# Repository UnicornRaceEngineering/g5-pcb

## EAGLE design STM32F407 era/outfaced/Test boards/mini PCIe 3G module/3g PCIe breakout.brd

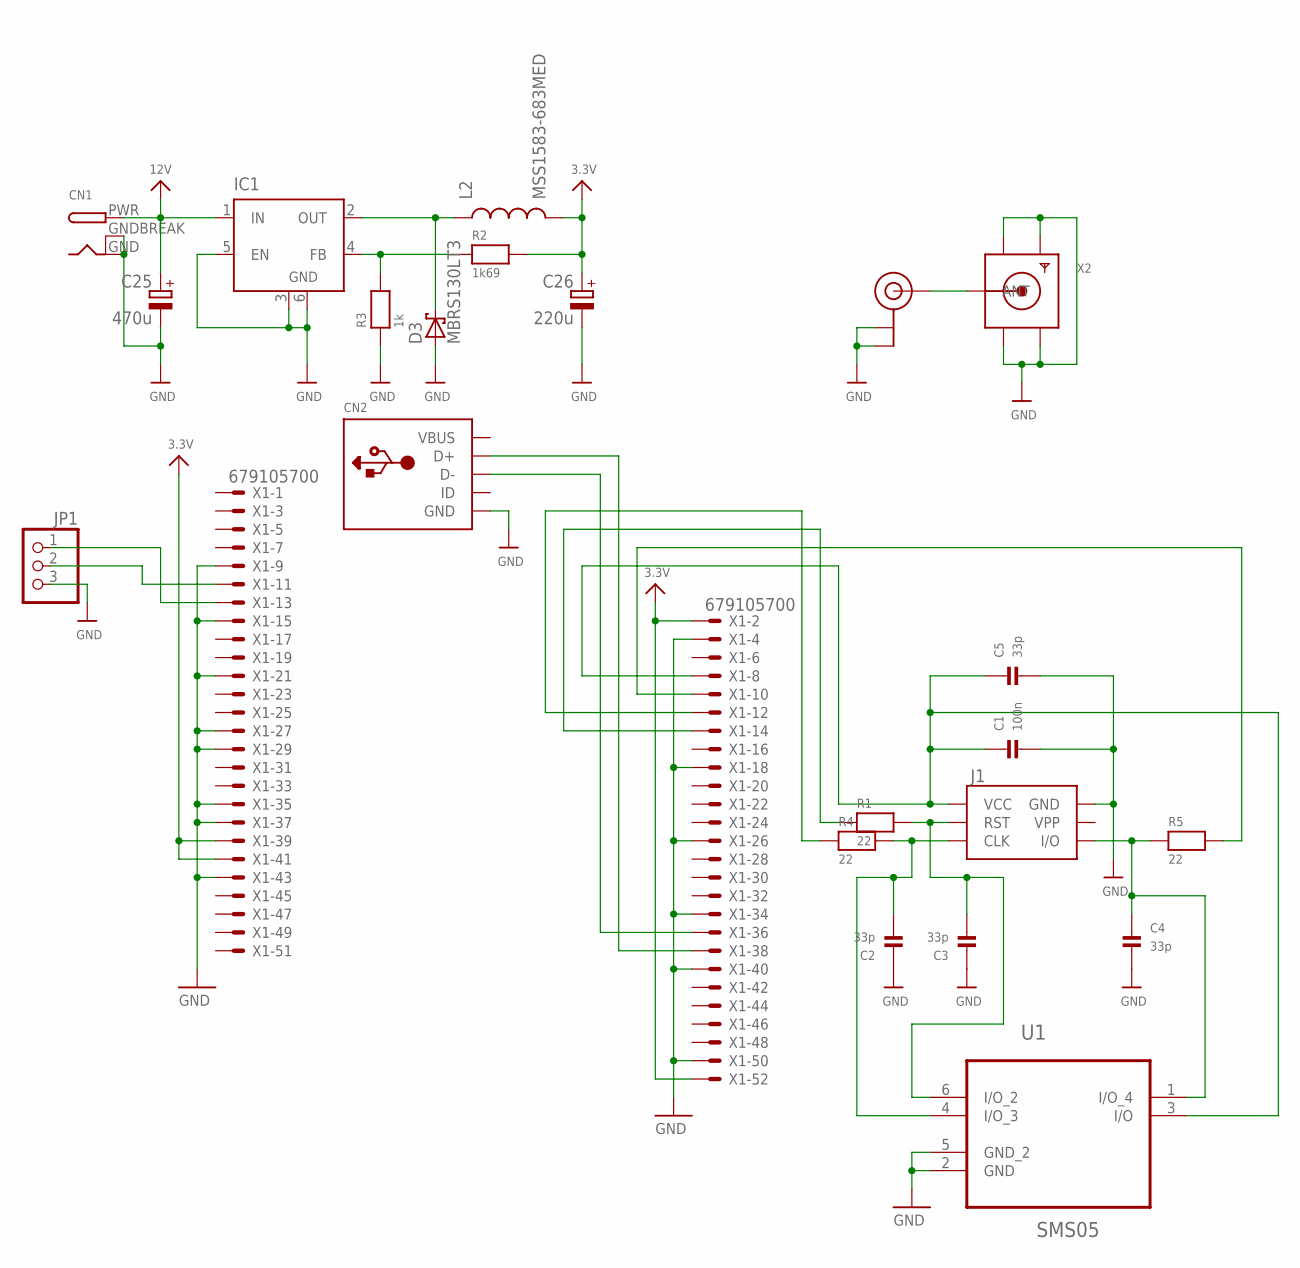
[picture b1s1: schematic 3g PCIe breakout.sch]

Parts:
C1: 100n; _0603
C2, C3, C4, C5: 33p; _0603
C25: 470u; 153CLV-1012
C26: 220u; 153CLV-1012
CN1: DCBARRELPTH; DCJACK_2MM_PTH
CN2: USBMINIB; USB-MINIB
D3: MBRS130LT3; SMB
IC1: LM2596S; TO263-5
J1: SIMHOLDERSIM; SIMHOLDER
JP1: PINHD-1X3; 1X03
L2: MSS1583-683MED; CDRH125
R1, R4, R5: 22; _0603
R2: 1k69; _0603
R3: 1k; _0603
U1: SMS05; SOT95P280X145-6N
U$12: U.FL
X1: 679105700
X2: SMACONNECTOR; SMA90_DIP

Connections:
3.3V: C26.+, L2.2, R2.2, X1.2, X1.39, X1.41, X1.52
12V: C25.+, CN1.PWR, IC1.1 (IN)
GND: C1.2, C2.1, C3.1, C4.2, C5.2, C25.-, C26.-, CN1.GND, CN1.GNDBREAK, CN2.GND, D3.A, IC1.3 (GND), IC1.5 (EN), IC1.6 (GND), J1.C5 (GND), JP1.3, R3.1, U1.2 (GND), U1.5 (GND_2), U$12.1 (GND), U$12.2 (GND), X1.4, X1.9, X1.15, X1.18, X1.21, X1.26, X1.27, X1.29, X1.34, X1.35, X1.37, X1.40, X1.43, X1.50, X2.GND1, X2.GND2, X2.GND3, X2.GND4
unnamed: CN2.D+, X1.38
unnamed: CN2.D-, X1.36
unnamed: JP1.1, X1.13
unnamed: JP1.2, X1.11
unnamed: C3.2, J1.C2 (RST), R1.2, U1.6 (I/O_2)
unnamed: D3.C, IC1.2 (OUT), L2.1
unnamed: C2.2, J1.C3 (CLK), R4.2, U1.4 (I/O_3)
unnamed: C4.1, J1.C7 (I/O), R5.1, U1.1 (I/O_4)
unnamed: IC1.4 (FB), R2.1, R3.2
unnamed: C1.1, C5.1, J1.C1 (VCC), U1.3 (I/O), X1.8
unnamed: R5.2, X1.10
unnamed: R1.1, X1.14
unnamed: R4.1, X1.12
unnamed: U$12.3 (SIGNAL), X2.ANTENNA (ANT)
VBUS: CN2.VBUS

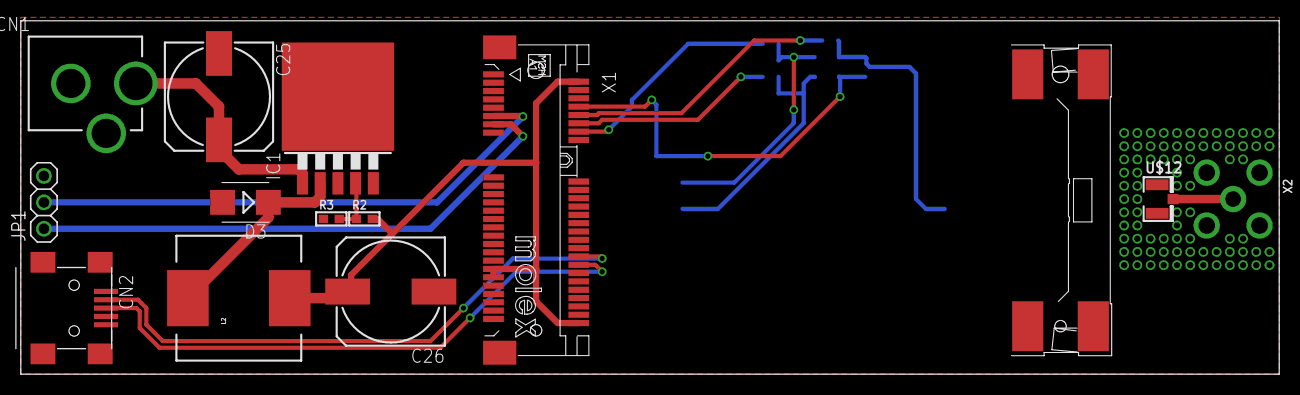
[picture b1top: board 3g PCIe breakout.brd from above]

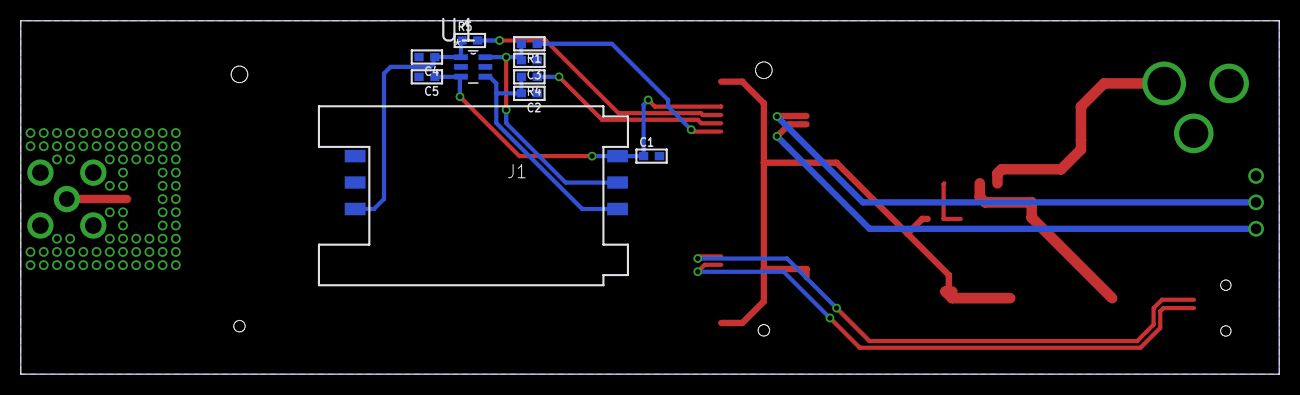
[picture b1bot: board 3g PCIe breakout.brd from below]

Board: 2 copper layers, 120.9 x 34.0 mm, 23 parts (10 on the bottom side), 17 nets.

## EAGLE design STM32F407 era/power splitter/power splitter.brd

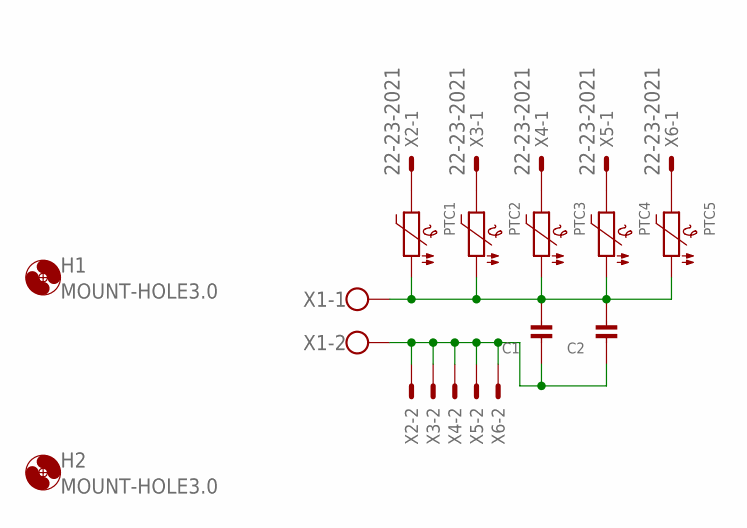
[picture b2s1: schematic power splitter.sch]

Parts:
C1, C2: CAP_CERAMIC_0805; _0805
H1, H2: MOUNT-HOLE3.0; 3,0
PTC1, PTC2, PTC3, PTC4, PTC5: PTC1206; 1206
X1: W237-102
X2, X3, X4, X5, X6: 22-23-2021

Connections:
unnamed: PTC1.2, X2.1
unnamed: PTC2.2, X3.1
unnamed: PTC3.2, X4.1
unnamed: PTC4.2, X5.1
unnamed: PTC5.2, X6.1
unnamed: C1.2, C2.2, PTC1.1, PTC2.1, PTC3.1, PTC4.1, PTC5.1, X1.1
unnamed: C1.1, C2.1, X1.2, X2.2, X3.2, X4.2, X5.2, X6.2

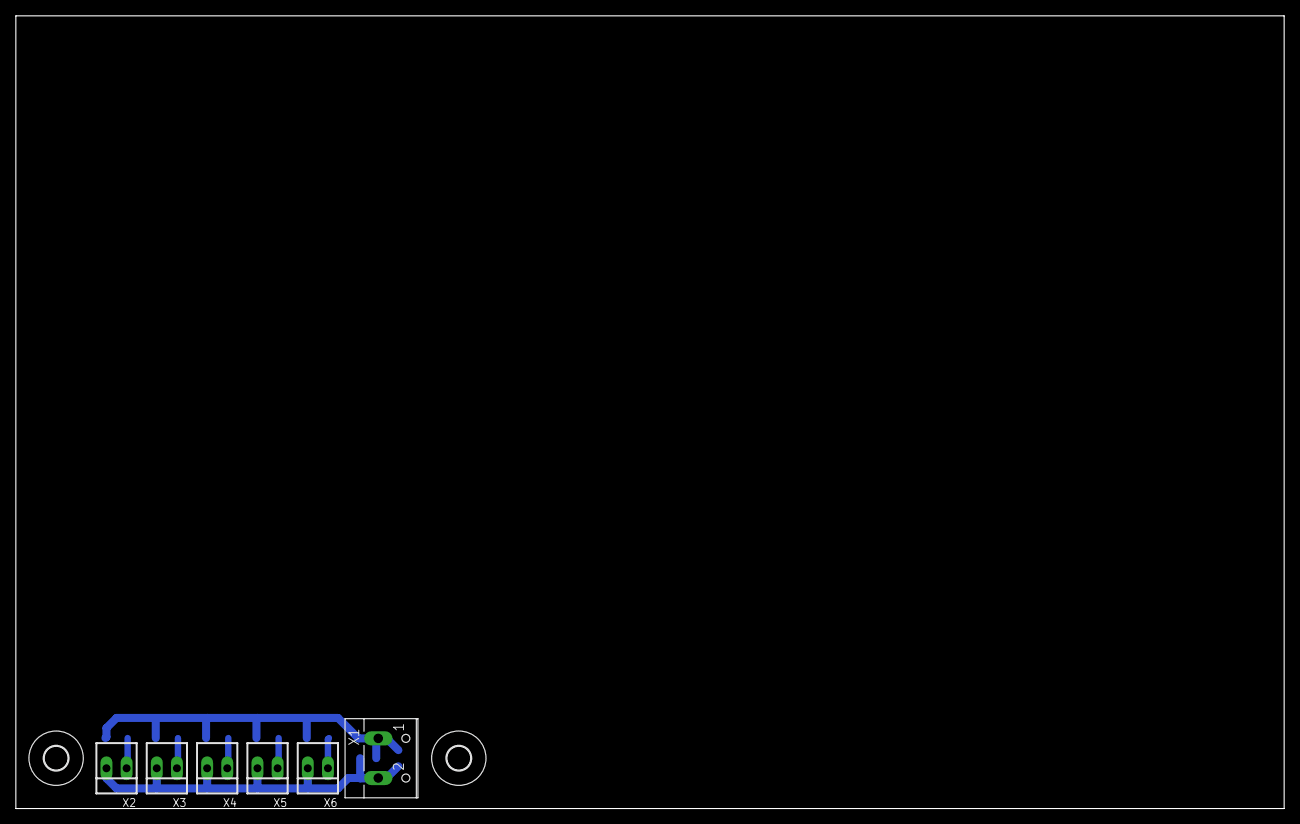
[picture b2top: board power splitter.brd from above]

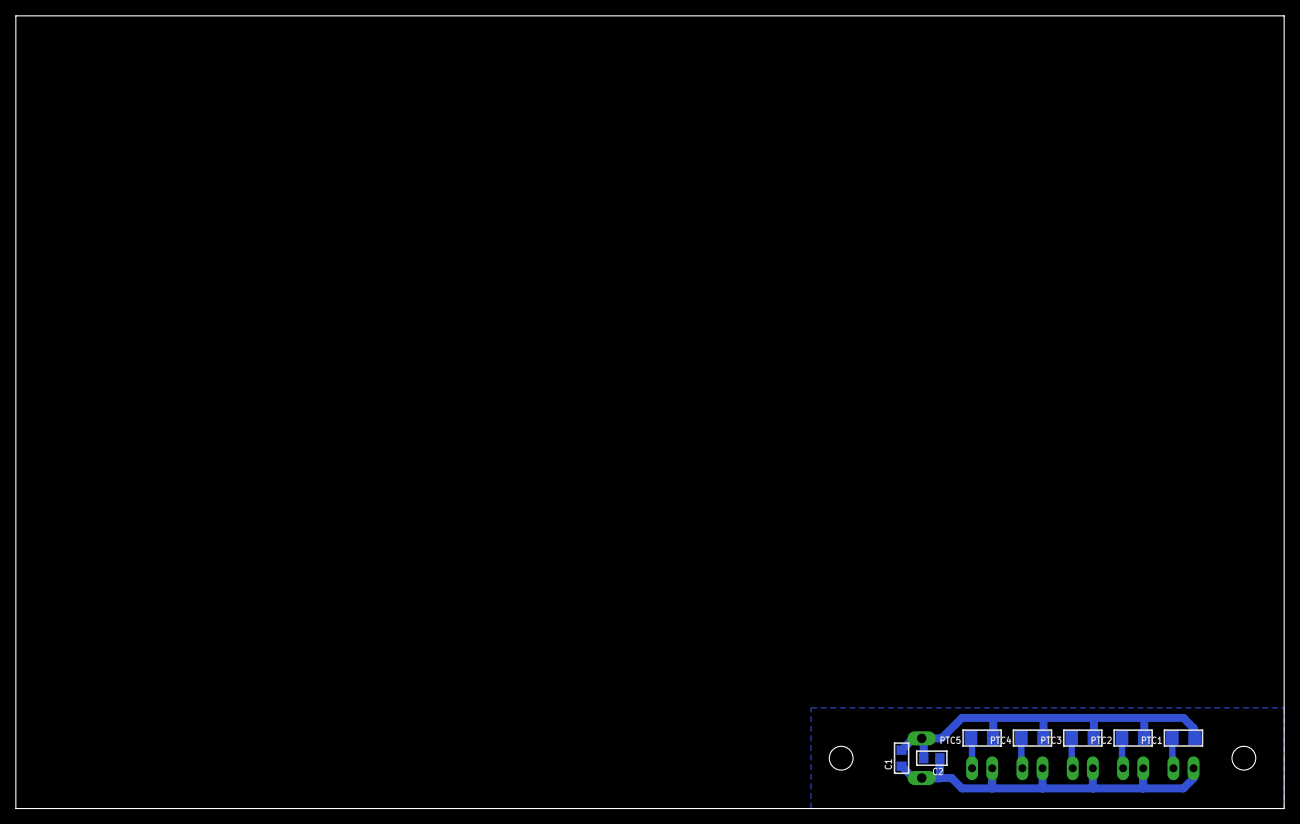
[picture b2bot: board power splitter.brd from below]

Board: 2 copper layers, 160.0 x 100.0 mm, 15 parts (7 on the bottom side), 7 nets.

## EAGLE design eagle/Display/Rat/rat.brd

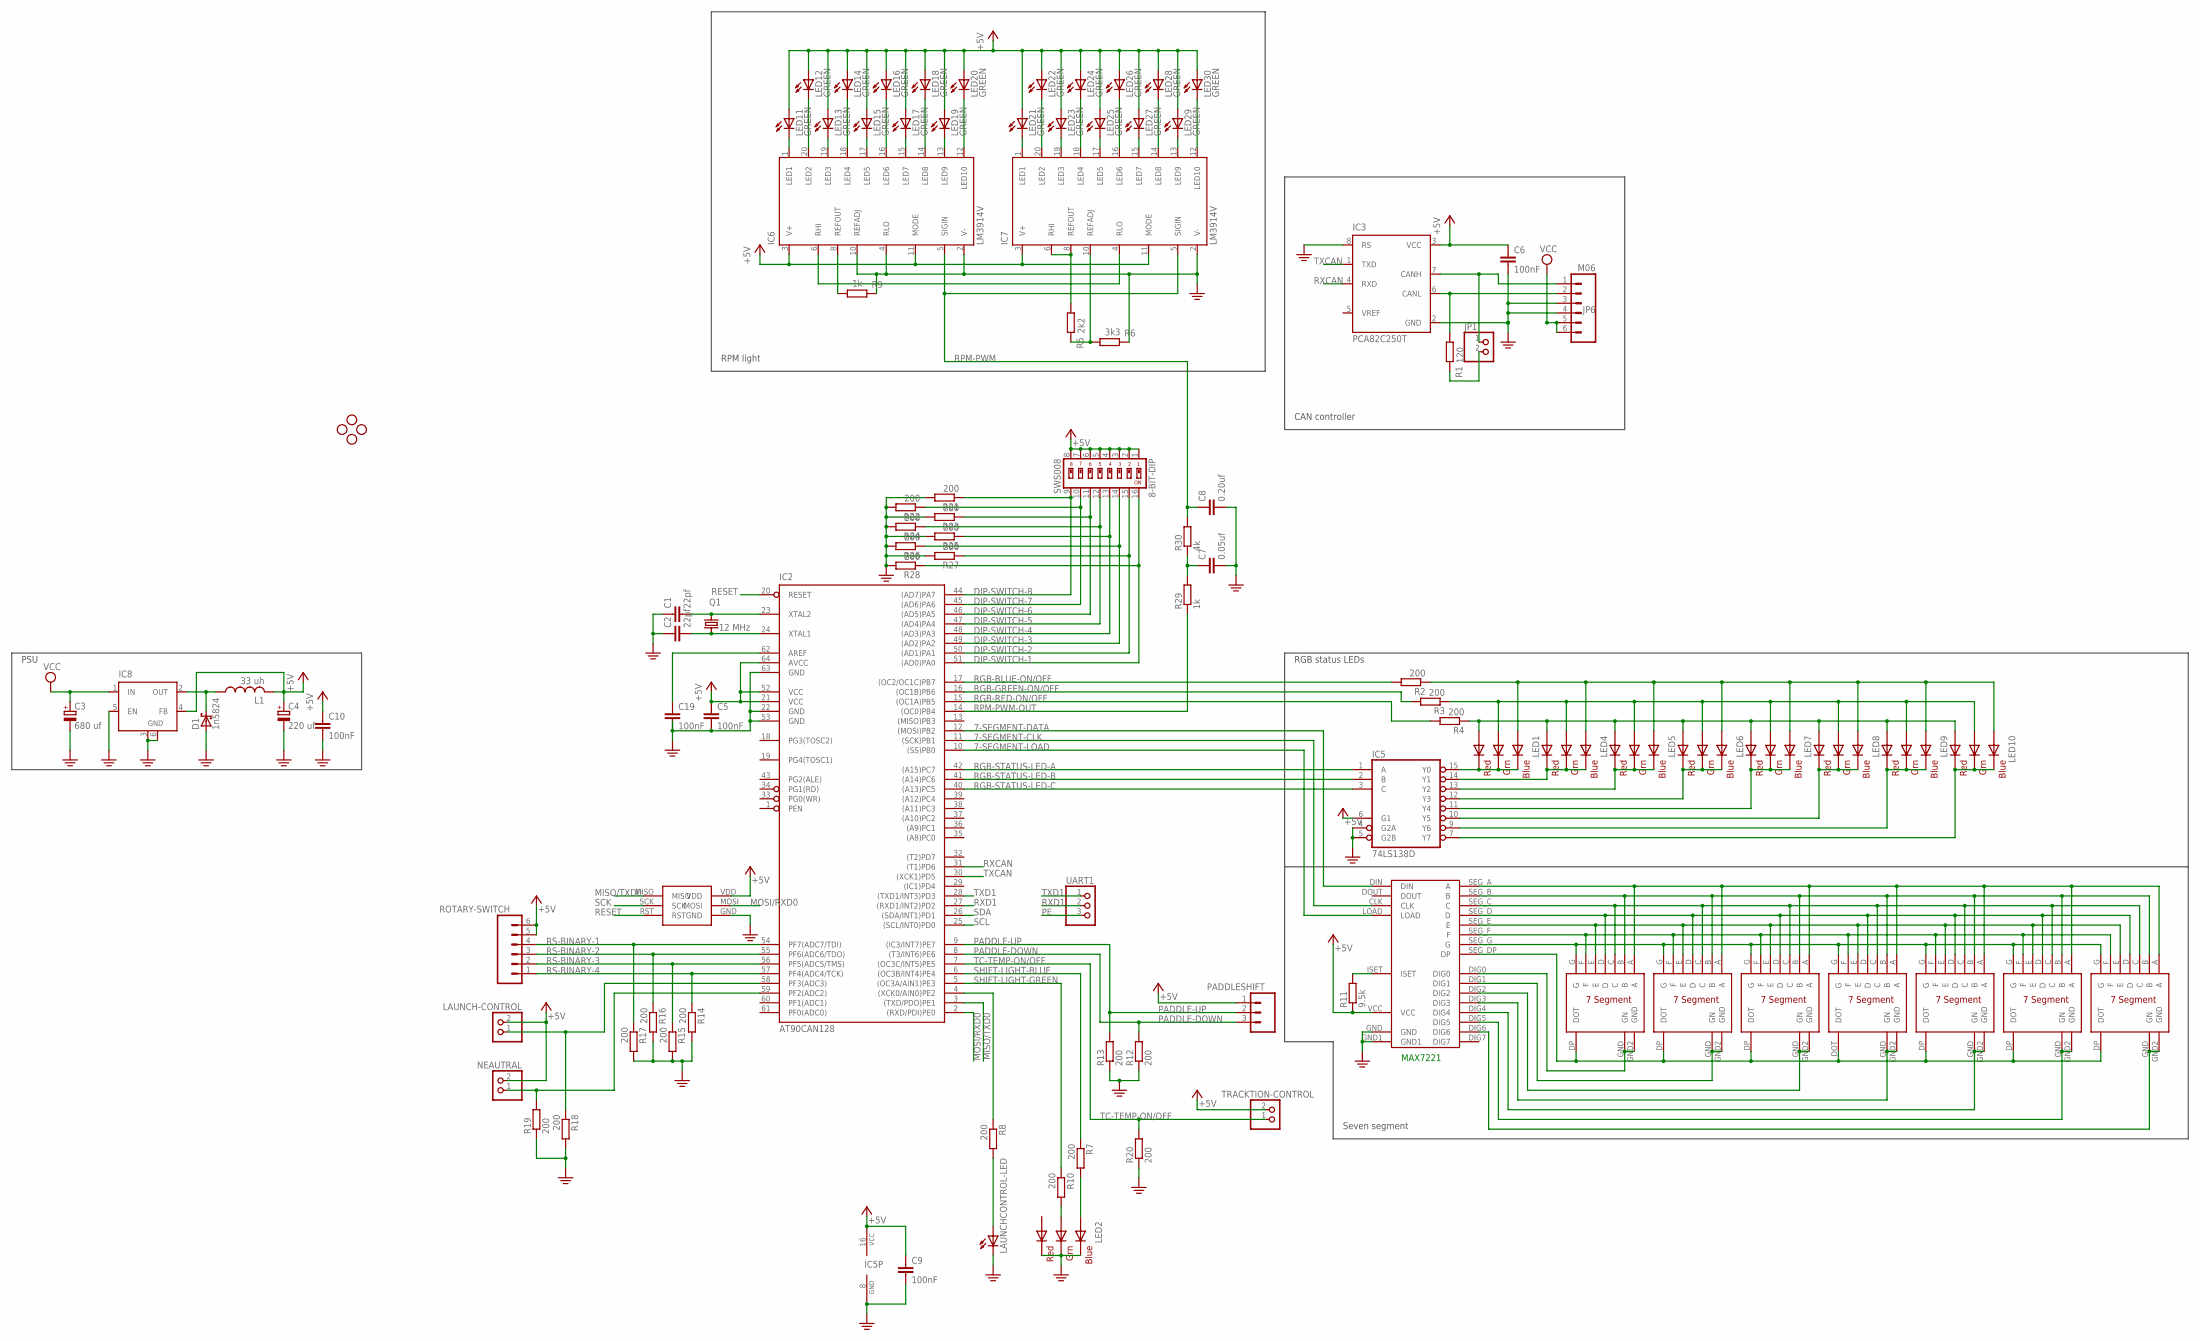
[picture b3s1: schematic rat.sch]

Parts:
8-BIT-DIP: SWS008; SMS-008
C1, C2: 22pf; C0603K
C3: 680 uf; E5-10,5
C4: 220 uf; E2,5-7
C5, C6, C9, C10, C19: 100nF; C0603K
C7: 0.05uf; C0603K
C8: 0.20uf; C0603K
D1: 1n5824; P6T15
IC2: AT90CAN128; TQFP64
IC3: PCA82C250T; SO8
IC5: 74LS138D; SO16
IC6, IC7: LM3914V; PLCC20S
IC8: LM2596S; TO263-5
JP1: PINHD-1X2; 1X02
JP2, JP3, JP4, JP5: STAND-OFF
JP6: M06; S6B_PH
L1: 33 uh; TFI0410
LAUNCH-CONTROL: JST_2PIN-SMT-RA; JST-PH-2-SMT-RA
LAUNCHCONTROL-LED: LEDSMT1206; 1206
LED1, LED2, LED4, LED5, LED6, LED7, LED8, LED9, LED10: RGBLED5050
LED11, LED12, LED13, LED14, LED15, LED16, LED17, LED18, LED19, LED20, LED21, LED22, LED23, LED24, LED25, LED26, LED27, LED28, LED29, LED30: GREEN; 1206
MAX7221: MAX7221-SMD; MAX7221
NEAUTRAL: JST_2PIN-SMT-RA; JST-PH-2-SMT-RA
PADDLESHIFT: M03; S3B-PH
Q1: 12 MHz; HC49U70
R1: 120; R0603
R2, R3, R4, R7, R8, R10, R12, R13, R14, R15, R16, R17, R18, R19, R20, R21, R22, R23, R24, R25, R26, R27, R28: 200; R0603
R5: 2k2; R0603
R6: 3k3; R0603
R9, R29: 1k; R0603
R11: 9.5k; R0603
R30: 4k; R0603
ROTARY-SWITCH: M06; S6B_PH
TRACKTION-CONTROL: JST_2PIN-SMT-RA; JST-PH-2-SMT-RA
U$2, U$3, U$4, U$6, U$7, U$8: REDSEVENSEGMENT; REDSEGMENT
U$5: BIGSEVENSEGMENT
U$9: ISP-HEADER
UART1: PINHD-1X3; 1X03

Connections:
7-SEGMENT-CLK: IC2.11 ((SCK)PB1), MAX7221.CLK
7-SEGMENT-DATA: IC2.12 ((MOSI)PB2), MAX7221.DIN
7-SEGMENT-LOAD: IC2.10 ((SS)PB0), MAX7221.LOAD
+5V: 8-BIT-DIP.1, 8-BIT-DIP.2, 8-BIT-DIP.3, 8-BIT-DIP.4, 8-BIT-DIP.5, 8-BIT-DIP.6, 8-BIT-DIP.7, 8-BIT-DIP.8, C4.+, C5.1, C6.1, C9.1, C10.1, IC2.21 (VCC), IC2.52 (VCC), IC2.64 (AVCC), IC3.3 (VCC), IC5.6 (G1), IC5.16 (VCC), IC6.3 (V+), IC6.11 (MODE), IC7.3 (V+), IC7.11 (MODE), IC8.4 (FB), L1.2, LAUNCH-CONTROL.2 (1), LED11.A, LED12.A, LED13.A, LED14.A, LED15.A, LED16.A, LED17.A, LED18.A, LED19.A, LED20.A, LED21.A, LED22.A, LED23.A, LED24.A, LED25.A, LED26.A, LED27.A, LED28.A, LED29.A, LED30.A, MAX7221.VCC, NEAUTRAL.2 (1), PADDLESHIFT.1, R11.1, ROTARY-SWITCH.5, ROTARY-SWITCH.6, TRACKTION-CONTROL.2 (1), U$9.VDD
CANJUMP1: IC3.7 (CANH), JP1.1, JP6.1
CANJUMP2: JP1.2, R1.2
DIP-SWITCH-1: 8-BIT-DIP.16, IC2.51 ((AD0)PA0), R28.1
DIP-SWITCH-2: 8-BIT-DIP.15, IC2.50 ((AD1)PA1), R27.1
DIP-SWITCH-3: 8-BIT-DIP.14, IC2.49 ((AD2)PA2), R26.1
DIP-SWITCH-4: 8-BIT-DIP.13, IC2.48 ((AD3)PA3), R25.1
DIP-SWITCH-5: 8-BIT-DIP.12, IC2.47 ((AD4)PA4), R24.1
DIP-SWITCH-6: 8-BIT-DIP.11, IC2.46 ((AD5)PA5), R23.1
DIP-SWITCH-7: 8-BIT-DIP.10, IC2.45 ((AD6)PA6), R22.1
DIP-SWITCH-8: 8-BIT-DIP.9, IC2.44 ((AD7)PA7), R21.1
MISO/TXD0: IC2.3 ((TXD/PDO)PE1), U$9.MISO
MOSI/RXD0: IC2.2 ((RXD/PDI)PE0), U$9.MOSI
unnamed: C2.2, IC2.24 (XTAL1), Q1.1
unnamed: C1.2, IC2.23 (XTAL2), Q1.2
unnamed: MAX7221.SEG_A (A), U$2.A, U$3.A, U$4.A, U$5.A, U$6.A, U$7.A, U$8.A
unnamed: MAX7221.SEG_B (B), U$2.B, U$3.B, U$4.B, U$5.B, U$6.B, U$7.B, U$8.B
unnamed: MAX7221.SEG_C (C), U$2.C, U$3.C, U$4.C, U$5.C, U$6.C, U$7.C, U$8.C
unnamed: C19.1, IC2.62 (AREF)
unnamed: MAX7221.SEG_D (D), U$2.D, U$3.D, U$4.D, U$5.D, U$6.D, U$7.D, U$8.D
unnamed: MAX7221.SEG_E (E), U$2.E, U$3.E, U$4.E, U$5.E, U$6.E, U$7.E, U$8.E
unnamed: MAX7221.SEG_F (F), U$2.F, U$3.F, U$4.F, U$5.F, U$6.F, U$7.F, U$8.F
unnamed: MAX7221.SEG_G (G), U$2.G, U$3.G, U$4.G, U$5.G, U$6.G, U$7.G, U$8.G
unnamed: MAX7221.DIG0, U$2.GND (GN), U$2.GND2 (GND)
unnamed: MAX7221.DIG1, U$3.GND (GN), U$3.GND2 (GND)
unnamed: MAX7221.DIG2, U$4.GND (GN), U$4.GND2 (GND)
unnamed: MAX7221.DIG3, U$5.GND (GN), U$5.GND2 (GND)
unnamed: MAX7221.DIG4, U$6.GND (GN), U$6.GND2 (GND)
unnamed: MAX7221.DIG5, U$7.GND (GN), U$7.GND2 (GND)
unnamed: MAX7221.DIG6, U$8.GND (GN), U$8.GND2 (GND)
unnamed: MAX7221.SEG_DP (DP), U$2.DP (DOT), U$3.DP (DOT), U$4.DP (DOT), U$5.DOT, U$6.DP (DOT), U$7.DP (DOT), U$8.DP (DOT)
unnamed: C7.1, R29.2, R30.1
unnamed: MAX7221.ISET, R11.2
unnamed: IC2.59 (PF2(ADC2)), NEAUTRAL.1 (2), R19.2
unnamed: LED1.2 (RED_A), LED4.2 (RED_A), LED5.2 (RED_A), LED6.2 (RED_A), LED7.2 (RED_A), LED8.2 (RED_A), LED9.2 (RED_A), LED10.2 (RED_A), R4.1
unnamed: LED1.1 (GREEN_A), LED4.1 (GREEN_A), LED5.1 (GREEN_A), LED6.1 (GREEN_A), LED7.1 (GREEN_A), LED8.1 (GREEN_A), LED9.1 (GREEN_A), LED10.1 (GREEN_A), R3.1
unnamed: LED1.3 (BLUE_A), LED4.3 (BLUE_A), LED5.3 (BLUE_A), LED6.3 (BLUE_A), LED7.3 (BLUE_A), LED8.3 (BLUE_A), LED9.3 (BLUE_A), LED10.3 (BLUE_A), R2.1
unnamed: IC5.15 (Y0), LED1.4 (BLUE_C), LED1.5 (RED_C), LED1.6 (GREEN_C)
unnamed: IC5.14 (Y1), LED4.4 (BLUE_C), LED4.5 (RED_C), LED4.6 (GREEN_C)
unnamed: IC5.13 (Y2), LED5.4 (BLUE_C), LED5.5 (RED_C), LED5.6 (GREEN_C)
unnamed: IC5.12 (Y3), LED6.4 (BLUE_C), LED6.5 (RED_C), LED6.6 (GREEN_C)
unnamed: IC5.11 (Y4), LED7.4 (BLUE_C), LED7.5 (RED_C), LED7.6 (GREEN_C)
unnamed: IC5.10 (Y5), LED8.4 (BLUE_C), LED8.5 (RED_C), LED8.6 (GREEN_C)
unnamed: IC5.9 (Y6), LED9.4 (BLUE_C), LED9.5 (RED_C), LED9.6 (GREEN_C)
unnamed: IC5.7 (Y7), LED10.4 (BLUE_C), LED10.5 (RED_C), LED10.6 (GREEN_C)
unnamed: D1.C, IC8.2 (OUT), L1.1
unnamed: IC6.1 (LED1), LED11.C
unnamed: IC6.20 (LED2), LED12.C
unnamed: IC6.19 (LED3), LED13.C
unnamed: IC3.6 (CANL), JP6.2, R1.1
unnamed: IC6.18 (LED4), LED14.C
unnamed: IC6.17 (LED5), LED15.C
unnamed: IC6.16 (LED6), LED16.C
unnamed: IC6.15 (LED7), LED17.C
unnamed: IC6.14 (LED8), LED18.C
unnamed: IC6.13 (LED9), LED19.C
unnamed: IC6.12 (LED10), LED20.C
unnamed: IC7.1 (LED1), LED21.C
unnamed: IC7.20 (LED2), LED22.C
unnamed: IC7.19 (LED3), LED23.C
unnamed: IC7.18 (LED4), LED24.C
unnamed: IC7.17 (LED5), LED25.C
unnamed: IC7.16 (LED6), LED26.C
unnamed: IC7.15 (LED7), LED27.C
unnamed: IC7.14 (LED8), LED28.C
unnamed: IC7.13 (LED9), LED29.C
unnamed: IC7.12 (LED10), LED30.C
unnamed: IC2.58 (PF3(ADC3)), LAUNCH-CONTROL.1 (2), R18.1
unnamed: IC6.6 (RHI), IC7.4 (RLO)
unnamed: IC7.6 (RHI), IC7.8 (REFOUT), R5.1
unnamed: IC7.10 (REFADJ), R5.2, R6.1
unnamed: IC6.8 (REFOUT), R9.1
unnamed: LED2.3 (BLUE_A), R7.2
unnamed: LED2.1 (GREEN_A), R10.2
unnamed: LAUNCHCONTROL-LED.A, R8.2
unnamed: IC2.4 ((XCK0/AIN0)PE2), R8.1
PADDLE-DOWN: IC2.8 ((T3/INT6)PE6), PADDLESHIFT.3, R12.2
PADDLE-UP: IC2.9 ((IC3/INT7)PE7), PADDLESHIFT.2, R13.2
PE: C1.1, C2.1, C3.-, C4.-, C5.2, C6.2, C7.2, C8.2, C9.2, C10.2, C19.2, D1.A, IC2.22 (GND), IC2.53 (GND), IC2.63 (GND), IC3.2 (GND), IC3.8 (RS), IC5.4 (G2A), IC5.5 (G2B), IC5.8 (GND), IC6.2 (V-), IC6.4 (RLO), IC6.10 (REFADJ), IC7.2 (V-), IC8.3 (GND), IC8.5 (EN), IC8.6 (GND), JP6.3, JP6.4, LAUNCHCONTROL-LED.C, LED2.4 (BLUE_C), LED2.5 (RED_C), LED2.6 (GREEN_C), MAX7221.GND, MAX7221.GND1, R6.2, R9.2, R12.1, R13.1, R14.2, R15.2, R16.2, R17.2, R18.2, R19.1, R20.1, R21.2, R22.2, R23.2, R24.2, R25.2, R26.2, R27.2, R28.2, U$9.GND, UART1.3
RESET: IC2.20 (RESET), U$9.RST
RGB-BLUE-ON/OFF: IC2.17 ((OC2/OC1C)PB7), R2.2
RGB-GREEN-ON/OFF: IC2.16 ((OC1B)PB6), R3.2
RGB-RED-ON/OFF: IC2.15 ((OC1A)PB5), R4.2
RGB-STATUS-LED-A: IC2.42 ((A15)PC7), IC5.1 (A)
RGB-STATUS-LED-B: IC2.41 ((A14)PC6), IC5.2 (B)
RGB-STATUS-LED-C: IC2.40 ((A13)PC5), IC5.3 (C)
RPM-PWM: C8.1, IC6.5 (SIGIN), IC7.5 (SIGIN), R30.2
RPM-PWM-OUT: IC2.14 ((OC0)PB4), R29.1
RS-BINARY-1: IC2.54 (PF7(ADC7/TDI)), R17.1, ROTARY-SWITCH.4
RS-BINARY-2: IC2.55 (PF6(ADC6/TDO)), R16.1, ROTARY-SWITCH.3
RS-BINARY-3: IC2.56 (PF5(ADC5/TMS)), R15.1, ROTARY-SWITCH.2
RS-BINARY-4: IC2.57 (PF4(ADC4/TCK)), R14.1, ROTARY-SWITCH.1
RXCAN: IC2.31 ((T1)PD6), IC3.4 (RXD)
RXD1: IC2.27 ((RXD1/INT2)PD2), UART1.2
SCK: U$9.SCK
SCL: IC2.25 ((SCL/INT0)PD0)
SDA: IC2.26 ((SDA/INT1)PD1)
SHIFT-LIGHT-BLUE: IC2.6 ((OC3B/INT4)PE4), R7.1
SHIFT-LIGHT-GREEN: IC2.5 ((OC3A/AIN1)PE3), R10.1
TC-TEMP-ON/OFF: IC2.7 ((OC3C/INT5)PE5), R20.2, TRACKTION-CONTROL.1 (2)
TXCAN: IC2.30 ((XCK1)PD5), IC3.1 (TXD)
TXD1: IC2.28 ((TXD1/INT3)PD3), UART1.1
VCC: C3.+, IC8.1 (IN), JP6.5, JP6.6

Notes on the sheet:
MAX7221
RPM light
CAN controller
RGB status LEDs
Seven segment
PSU

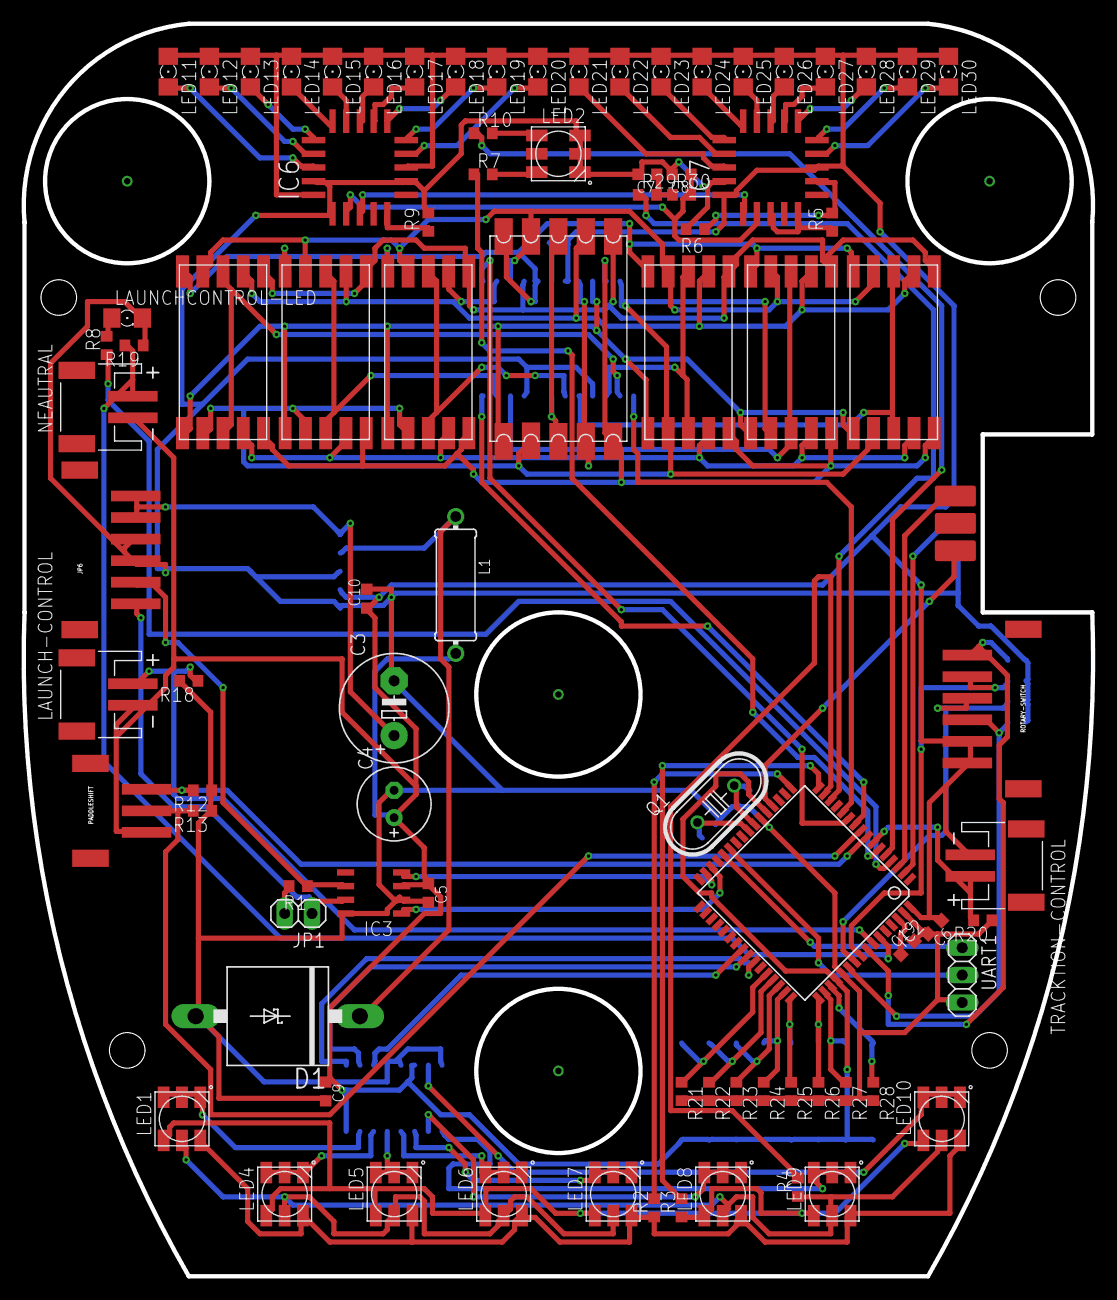
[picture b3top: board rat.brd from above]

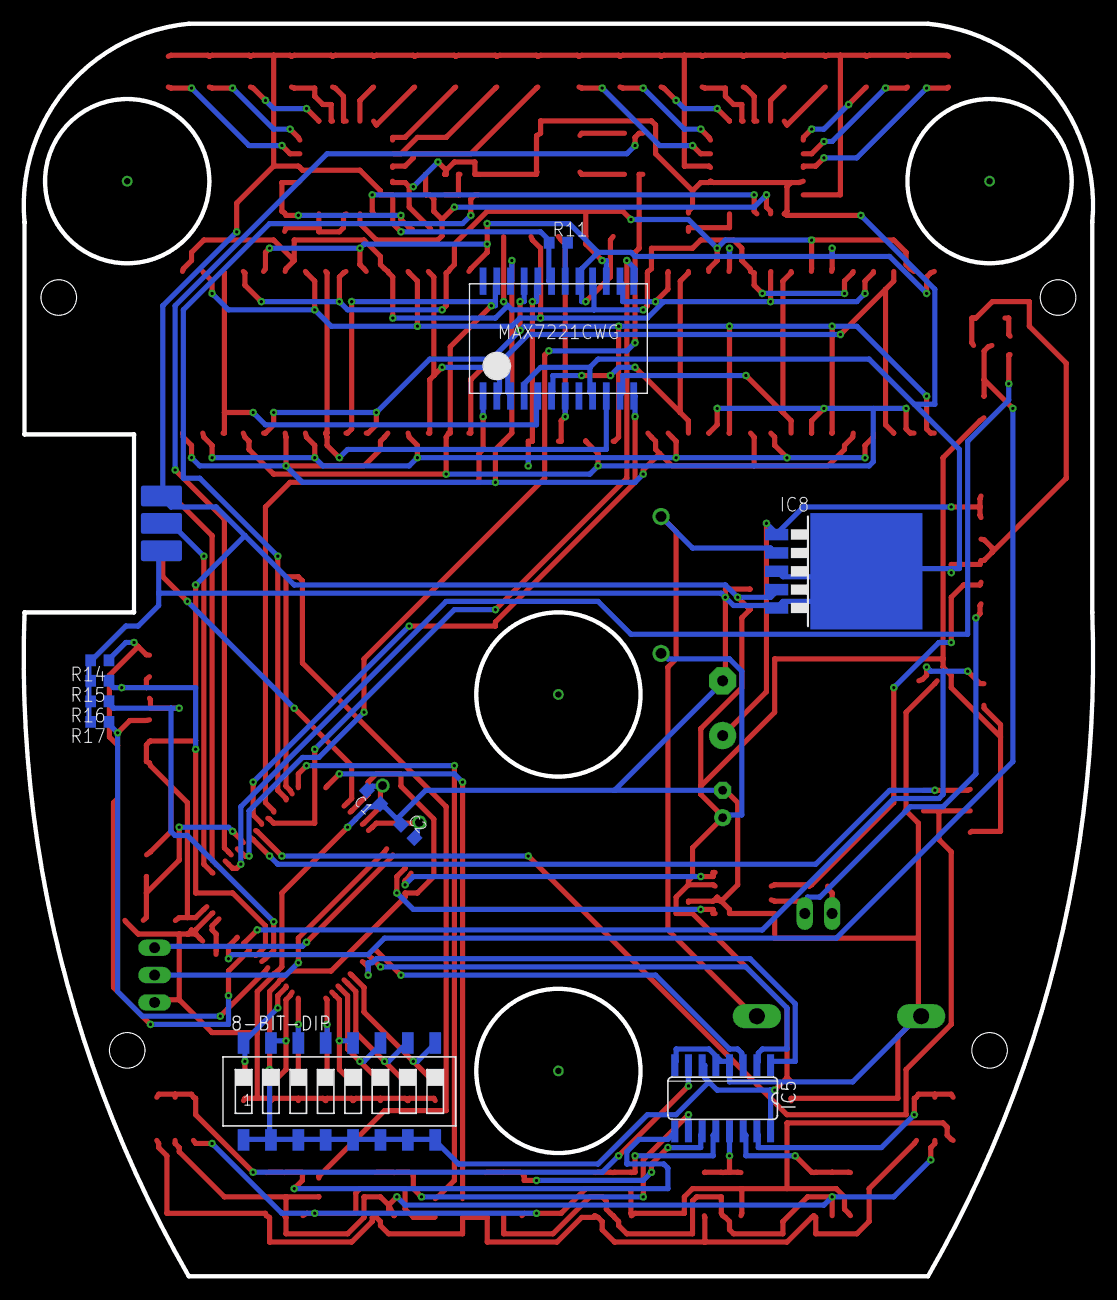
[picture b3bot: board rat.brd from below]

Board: 2 copper layers, 99.2 x 116.2 mm, 102 parts (11 on the bottom side), 103 nets.

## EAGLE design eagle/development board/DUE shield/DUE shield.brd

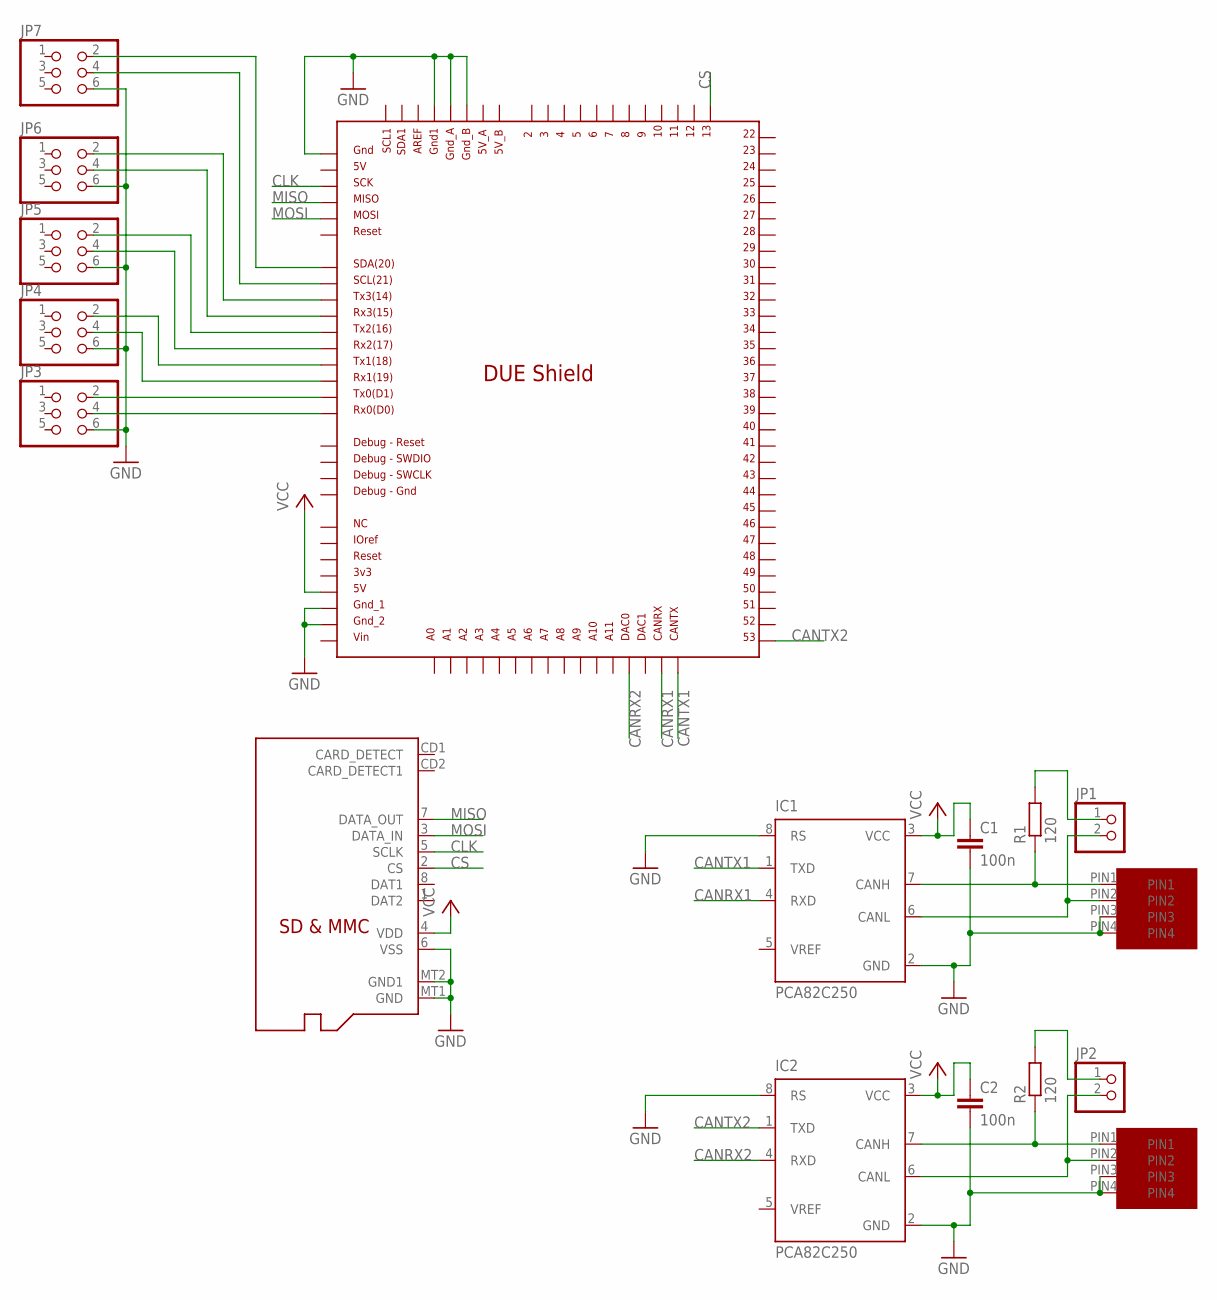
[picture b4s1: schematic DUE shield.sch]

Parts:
C1, C2: 100n; C050-024X044
IC1, IC2: PCA82C250; DIL08
JP1, JP2: PINHD-1X2; 1X02
JP3, JP4, JP5, JP6, JP7: PINHD-2X3; 2X03
R1, R2: 120; 0204/7
U$1: DUE(NORMAL)
U$2, U$3: MICROFIT4; MICROFIT4SOCK
U$4: MICROSD

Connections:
CANRX1: IC1.4 (RXD), U$1.CANRX
CANRX2: IC2.4 (RXD), U$1.DAC0
CANTX1: IC1.1 (TXD), U$1.CANTX
CANTX2: IC2.1 (TXD), U$1.53
CLK: U$1.SCK_ICSP, U$4.5 (SCLK)
CS: U$1.13, U$4.2 (CS)
GND: C1.2, C2.2, IC1.2 (GND), IC1.8 (RS), IC2.2 (GND), IC2.8 (RS), JP3.6, JP4.6, JP5.6, JP6.6, JP7.6, U$1.5V_ICSP, U$1.GND1, U$1.GND_1, U$1.GND_2, U$1.GND_A, U$1.GND_B, U$2.PIN3, U$2.PIN4, U$3.PIN3, U$3.PIN4, U$4.6 (VSS), U$4.MT1 (GND), U$4.MT2 (GND1); also elsewhere on the board
MISO: U$1.MISO_ICSP, U$4.7 (DATA_OUT)
MOSI: U$1.MOSI_ICSP, U$4.3 (DATA_IN)
unnamed: IC1.7 (CANH), R1.1, U$2.PIN1
unnamed: IC1.6 (CANL), JP1.2, U$2.PIN2
unnamed: JP1.1, R1.2
unnamed: JP6.2, U$1.TX3
unnamed: IC2.7 (CANH), R2.1, U$3.PIN1
unnamed: IC2.6 (CANL), JP2.2, U$3.PIN2
unnamed: JP2.1, R2.2
unnamed: JP6.4, U$1.RX3
unnamed: JP5.2, U$1.TX2
unnamed: JP5.4, U$1.RX2
unnamed: JP4.2, U$1.TX1
unnamed: JP4.4, U$1.RX1
unnamed: JP3.2, U$1.TX0
unnamed: JP3.4, U$1.RX0
unnamed: JP7.4, U$1.SCL
unnamed: JP7.2, U$1.SDA
unnamed 40: U$1.SCL1; also elsewhere on the board
unnamed 41: U$1.SDA1; also elsewhere on the board
VCC: C1.1, C2.1, IC1.3 (VCC), IC2.3 (VCC), U$1.5V, U$4.4 (VDD)

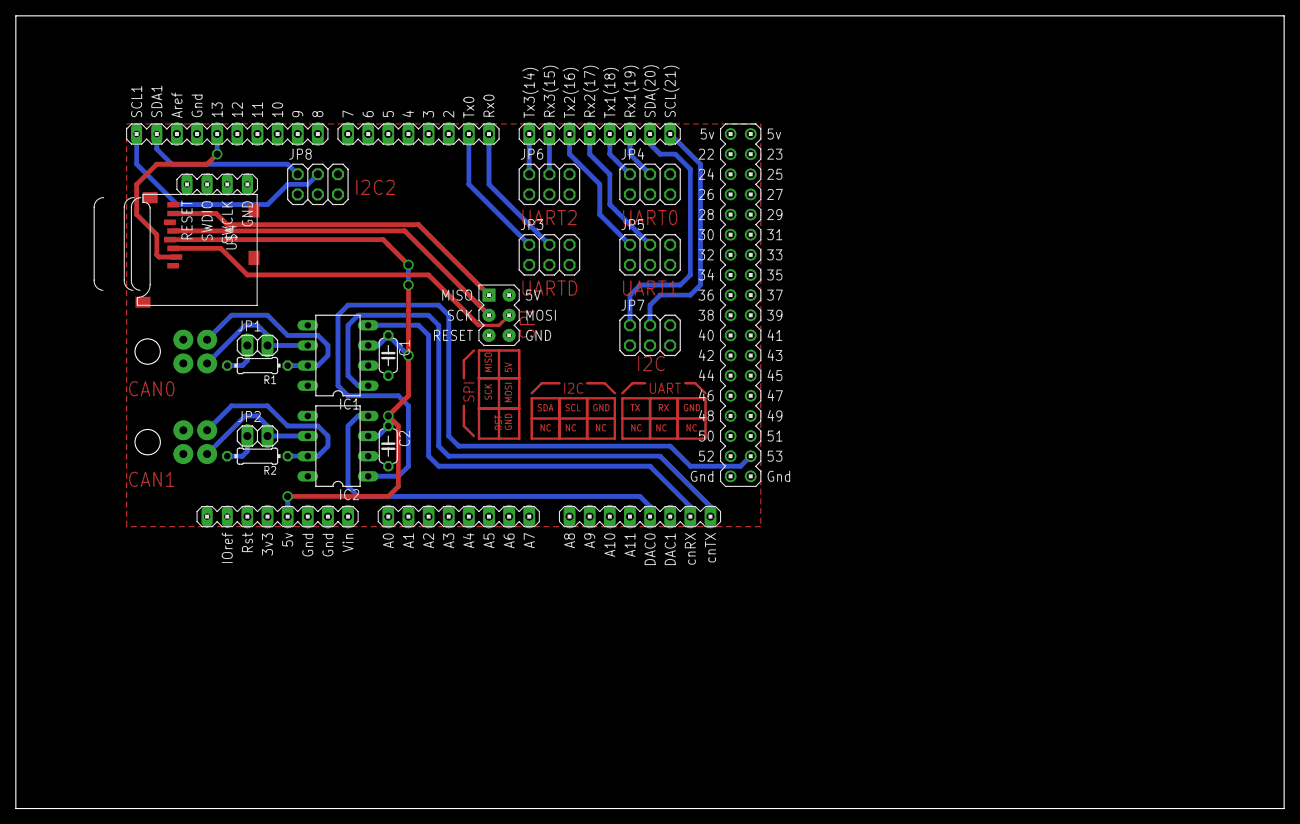
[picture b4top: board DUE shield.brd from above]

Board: 2 copper layers, 160.0 x 100.0 mm, 18 parts (0 on the bottom side), 28 nets.

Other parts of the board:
JP8: 2X03

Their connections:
GND: JP8.6; also elsewhere on the board
unnamed 40: JP8.4; also elsewhere on the board
unnamed 41: JP8.2; also elsewhere on the board

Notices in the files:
parts and their libraries:
microbuilder: This work is placed in the public domain, and may be freely used for commercial and non-commercial work with the following conditions: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
SparkFun-Passives: Licensing: Creative Commons ShareAlike 4.0 International - https://creativecommons.org/licenses/by-sa/4.0
